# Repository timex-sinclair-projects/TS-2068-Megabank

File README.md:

# TS-2068 Megabank

A battery-backed 4 MB RAM board for the Timex Sinclair 2068, built the way
Timex meant memory to grow: as **expansion banks** that can take over any 8K
chunk of the address space. It is a card for the expansion bus, for owners
of the TS-Pico v3.

It gives the 2068:

- **Paged memory:** any 8K page of the 4 MB, mapped into any chunk with two
  `OUT`s, at full memory speed.
- **A RAM disk:** `SAVE "r:name"`, `LOAD "r:name"`, `CAT "r:"` and the rest,
  kept through power-off by a battery.

**Status:** design. Nothing is built yet. Start with the
[specification](docs/spec.md); the board's KiCad project (schematic done,
routed on the TS-Pico v3's form factor, DRC clean, not yet ordered) is in
[hardware/](hardware/README.md).

*The routed card (KiCad render, 2026-11-07), the same 130 × 64 mm shape as
the TS-Pico v3. Underside: [docs/images/megabank-bottom.png](docs/images/megabank-bottom.png).*

## Where the work lives

| Part | Repository |
|---|---|
| The board: schematic, PCB, the controller's firmware | here |
| The TS-Pico ROM (detection, the RAM disk's copy routine, `r:`, the Timex bank API) and the v3 firmware (bus sharing, the RAM disk's file system) | [tspico-firmware-build](https://github.com/timex-sinclair-projects/tspico-firmware-build) |
| PicoVideo's support (ignoring screen writes to mapped banks) | [PicoVideo](https://github.com/timex-sinclair-projects/PicoVideo) |
| The emulator model | [zesarux-tspico](https://github.com/timex-sinclair-projects/zesarux-tspico) |

## The first test

Does a 2068 answer the board's ports, FCh and FDh? With nothing plugged in:

```
OUT 252,2: OUT 253,2: PRINT IN 252, IN 253
```

The border should not change, and nothing should answer either port.

**Result (2026-10-16), with the TS-Pico fitted:** the border did not change,
and both ports drift between 127 and 255 from one read to the next whatever
keys are held: a floating bus, with nothing answering. FCh and FDh stand.

## Licences

| What | Licence | File |
|---|---|---|
| Hardware design files: schematic and PCB | CERN Open Hardware Licence v2, Permissive (CERN-OHL-P-2.0) | [LICENSE-hardware.txt](LICENSE-hardware.txt) |
| Software: the board's controller firmware (RP2350B), tools and test programs | MIT | [LICENSE](LICENSE) |
| Documentation (`docs/`, this README) | Creative Commons Attribution 4.0 (CC BY 4.0) | [LICENSE-docs.txt](LICENSE-docs.txt) |

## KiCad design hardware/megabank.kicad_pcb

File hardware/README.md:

# Megabank KiCad project

Status 2026-11-07: **routed, DRC clean at every severity** (no errors, no warnings,
nothing unconnected), not yet ordered. The board has the TS-Pico v3's form factor
and is built with v3's script pipeline (tspico-hardware, `hardware/scripts/`),
copied here and renamed. Spec: [../docs/spec.md](../docs/spec.md).

- **Schematic:** four sheets, generated. ERC: one warning, expected (below).
- **Board:** outline, gold fingers and mounting holes are v3's. Routed by
  `scripts/flow.py` with Freerouting 2.4.1 and no hand edits: 1945 track
  segments (1315 top, 630 bottom), 355 vias, all 0.6/0.3 mm, narrowest track
  0.11 mm, nothing on the plane layers. Closed on the first attempt (re-routed
  2026-11-07 for the core LDO, which replaced the RP2350B's switcher and L1,
  and the GPIO46/47 test pads). Silkscreen: all 90 designators placed.
- **Fab files:** `python3 scripts/gen_fab.py` writes the Gerbers, BOM and CPL
  to `fab/jlcpcb/`, committed: `megabank-gerbers.zip`, `megabank-bom.csv`,
  `megabank-cpl.csv`, ready to upload as they are (the unzipped Gerbers are not
  committed); `fab/NOTES.md` lists what to check on upload.
- **Parts:** every fitted part has an LCSC number. $26.63 a board in parts at
  10 boards (`jlc_price.py`, 2026-11-07; it counts U1-U4 once, so about $27),
  plus $45 in extended-part fees once; the two SRAMs are $20.86 of it. The
  ME6211C12 LDO (32,146 in stock) is an extended part like the L1 it replaced.

## Form factor

The same card as v3, so the two share the extender, brackets and standoffs:

| Item | Value |
|---|---|
| Board | 130.00 x 64.25 mm, 1.6 mm, 4 layers (JLC04161H-7628): F.Cu, In1 GND, In2 +3V3, B.Cu |
| Body | 130.00 x 56.00 mm |
| Tongue | 83.66 x 8.25 mm, left edge 18.48 mm from the board's left edge, 1 mm chamfers |
| Fingers | `TS2068_EdgeConnector_2x32`, 32 positions at 2.54 mm, 31 a side, key slot at position 6 |
| Holes | M3 at (5, 5), (113.6, 4.2), (5, 51), (112, 51.5): v3's |

The finger geometry and the side-A-is-top assumption are v3's; see v3's
`hardware/README.md`, "Edge connector geometry". Check side A before ordering
(spec, open question 6).

## Sheets

| Sheet | Generator | Contents |
|---|---|---|
| `megabank.kicad_sch` | by hand | Root: four sheets, flat, global labels |
| `interface.kicad_sch` | `gen_interface.py` | P1 fingers; U1/U2 address buffers (always on: BA0-BA15), U3 data buffer (DIR = /RD, /OE = nDOE), U4 control buffer; U5 74LVC1G06 /BE driver; U6 74LVC1G06 /NMI driver; U7 74LVC2G34 /INT and /NMI in; pulls R1-R4 |
| `memory.kicad_sch` | `gen_memory.py` | U10/U11 CY62167EV30 as 2M x 8; U12 /WE gate; ~CE1 pull-downs, WINH pull-up, BHE/BLE links |
| `mcu.kicad_sch` | `gen_mcu.py` | v3's RP2350B core, same designators, but DVDD from U23, a 1.2 V LDO (no L1); USB-C; RUN, BOOTSEL; SW5 write protect; TP4/TP5 on the spare GPIOs; the GPIO map |
| `power.kicad_sch` | `gen_power.py` | +5V diode-OR (edge, USB), TLV1117LV33, TPS3839 -> CE2, LM66200 -> VSRAM, CR2032, battery monitor |

`gen_symbols.py` writes `lib/megabank.kicad_sym`: the edge connector (v3's),
the CY62167EV30 (from the Infineon datasheet, 002-24706 Rev \*B, figure 2) and
the LM66200 (TI SLVSG04, table 5-1). `parts.py` maps value and footprint to MPN
and LCSC number; `schlib.place()` stamps them on each symbol.

### GPIO map

A PIO state machine sees 32 pins, from GPIO0 or GPIO16. The port program needs
data, A0-A7 and the strobes; the memory program needs the chunk bits, the
strobes, /BE, the ~CE1s and the page bits. Everything both need sits in 16-31:

| GPIO | Net | |
|---|---|---|
| 0-7 | SD0-SD7 | SRAM-side data: `IN`/`OUT` to FCh/FDh |
| 8-15 | BA0-BA7 | port decode |
| 16-18 | BA13-BA15 | chunk (`out pc, 3`) |
| 19-25 | nMREQ_L, nIORQ_L, nRD_L, nWR_L, nRFSH_L, nM1_L, nRESET_L | |
| 26 | nDOE | data buffer enable, pulled up |
| 27 | BE_REQ | to U5, pulled down |
| 28-29 | nCE1_0, nCE1_1 | SRAM enables, pulled down |
| 30-37 | PA13-PA20 | page bits, contiguous with the ~CE1s |
| 38 | WINH | write inhibit, pulled up |
| 39 | nWP | write-protect switch, low = protected |
| 40 | BAT_ADC | ADC0 |
| 41 | BAT_EN | |
| 42 | nBE_L | /BE read back through U4's spare channel |
| 43 | nINT_L | /INT, through U7 |
| 44 | nNMI_L | /NMI, through U7 |
| 45 | NMI_REQ | to U6, pulled down (R4) |
| 46-47 | GP46, GP47 | spare, on test pads TP4, TP5 (silk "GP46", "GP47") for bench experiments |

### Decisions taken here, beyond the spec

- **USB-C, as on v3** (open question 11): firmware by BOOTSEL and the settings
  (`BASE`, `SIZE`) over USB. VBUS is diode-ORed with the edge +5V, so the board
  runs from USB alone on the bench. SWD pads TP1-TP3 too.
- **/BE read back:** U4's eighth channel brings /BE in as nBE_L (GPIO42), for
  timing on the bench and to see v3 serve a chunk.
- **BT1 is a Keystone 3034TR** (C5213768, 2026-11-07), the footprint's own
  part, as on the OpenSpand card, where JLCPCB placed it. The Q&J
  CR2032-BS-6-1 (C70377) made JLCPCB move the order to Standard PCBA (edge
  rails, which would sit against the fingers). Stock is thin (654); if it runs
  out, leave BT1 off and fit a Keystone 3034 from DigiKey (36-3034-ND) by hand.
- **R3, a /BE pull-up to +5V_EDGE, DNP** (open question 13): the bus already has
  v3's 2k2; the pad is there if the prototype shows /BE rising too slowly.
- **An LDO for the core, not the on-chip switcher** (2026-11-07): U23, an
  ME6211C12M5G-N (SOT-23-5, C236672), supplies DVDD at 1.2 V, as on the
  OpenSpand card. The switcher's inductor (v3's L1, Abracon
  AOTA-B201610S3R3-101-T) was the scarcest part on the board (3 at JLCPCB in
  October) and needed a pre-order or hand fitting. VREG_LX is open, VREG_FB is
  grounded, VREG_VIN (C22) and VREG_AVDD (R28/C39) stay powered (RP2350
  datasheet 6.3.7). 1.2 V is what v3's firmware sets for 250 MHz; the firmware
  may put the unused regulator in HIZ to save about 400 µA. C40 (1 µF) at the
  LDO's input, C20 (4.7 µF) at its output; C21/C47/C48 stay at DVDD pins 51,
  32 and 10.
- **Test pads on the spare GPIOs:** TP4 (GPIO46) and TP5 (GPIO47), for bench
  experiments such as a second controller's handshake (spec, Bus mastering).
- **One 0 R each for BHE and BLE** (R13, R14), shared by both chips.
- **Battery-monitor designators** are R51-R54, C55 (the spec's R1-R4, C1).
- **SRAM pins may be swapped at layout:** any permutation of A0-A20 or of
  I/O0-I/O7 is harmless, since both chips always see the same mapping. Only
  SDn must stay on GPIOn. Worth using if the router struggles.

### The ERC warning

`U5 pin 4 (open collector) and U4 pin 18 (tri-state)`: the /BE driver and the
buffer that reads /BE back. That is the intent.

## Layout

Coordinates in mm from the body's top-left corner (`gen_layout.py`, table `P`).

- **Over the fingers,** as v3: data U3 (x 40), high address U2 (x 63) over
  A15-A8, control U4 (x 80) over /MREQ to /RFSH, /BE driver U5 by finger A29.
  /INT and /NMI over their fingers (A14, A15) between C3 and U2: U7 (x 51.5),
  U6 and R4 (x 56.5).
  Low address U1 above U2.
- **RP2350B cluster** at v3's coordinates with v3's designators (U20 at
  (62, 26), 90°), so v3's crystal and fan-out pre-routes carry over. Flash U21
  to its left.
- **Core supply:** with VREG_FB grounded, pin 51 is the only DVDD pin a track
  can reach from outside the pad ring (on v3 the switcher's output came in
  through FB). So the LDO U23 sits above pin 51, at (60.55, 14.6), pins 4/5
  towards the chip: its output runs straight down to pin 51, 0.3 mm wide,
  past C21, with C20 off its side, and v3's DVDD spine under the package
  carries it on to pins 10 and 32. C40 above U23; plane vias for its input
  and ground. FB goes to a GND via where L1 was. TP4/TP5 at (53.5, 13.5) and
  (53.5, 16), up and left of the chip's GPIO46/47 pins.
  One pre-route changed: on v3, supply pin 29 dropped into the lanes of pads 27
  and 28 to reach its via, because those GPIOs (26, 27) were spare. Here they
  are nDOE and BE_REQ, and the first run left both sealed in on all three
  attempts. The 24/29 supply link now carries on under the package to pin 15,
  whose fan via is already on the +3V3 plane.
- **SRAM** U10 and U11 on the right, leads top and bottom; the /WE gate, the
  supervisor and the pulls in the strip between them and the crystal.
- **Power:** diodes and LDO top left, LM66200 and the battery monitor in the
  free strip above the RP2350B, the CR2032 bottom left. USB-C on the left edge
  (v3's place). RUN and BOOTSEL on the top edge (v3's places). Write-protect
  slide switch on the right edge.

## Next

1. **Check footprints against drawings:** the MSK12C02's
   actuator should face the right edge; TSOP-I 48 against Infineon's 51-85183.
   Then check side A of the fingers (spec, open question 6).
2. **The SRAM rail with a fresh cell:** the LM66200 passes whichever input is
   higher, and a new CR2032 reads up to about 3.3 V open circuit, against +3V3's
   3.25-3.35 V. At SRAM standby currents the cell may carry the rail some of the
   time with the 2068 on. Harmless to the data; it costs battery life. Measure on
   the prototype (spec, hardware test 3); a Schottky in series with the cell
   would settle it if needed.
3. **Stock:** 42 CY62167EV30 at JLCPCB on 2026-10-18, 40 on 2026-11-07, enough for 20 boards.

## Routing

```bash
cd hardware
PY=/Applications/KiCad/KiCad.app/Contents/Frameworks/Python.framework/Versions/Current/bin/python3
$PY scripts/flow.py                                   # jar from $FREEROUTING_JAR (or --jar); needs Homebrew's openjdk
scripts/check.sh                                      # ERC (one expected warning) and DRC
python3 scripts/gen_fab.py
```

`flow.py` regenerates the placement and discards all routing, then pre-routes,
autoroutes, finishes and places silkscreen, up to three attempts; Freerouting
does not give the same result twice. Each attempt took 4-8 minutes to route
here. A failed attempt is kept as `fab/route/attempt-N.kicad_pcb`.

## Regenerating

```bash
cd hardware
python3 scripts/gen_symbols.py                       # project symbols
for s in interface memory mcu power; do python3 scripts/gen_$s.py; done
PY=/Applications/KiCad/KiCad.app/Contents/Frameworks/Python.framework/Versions/Current/bin/python3
$PY scripts/gen_layout.py                            # skeleton, netlist, placement, planes (discards routing)
$PY scripts/preroute.py                              # v3's locked pre-routes
```

Regenerating a sheet overwrites hand edits; once a sheet is edited in KiCad,
retire its generator. The same goes for `gen_layout.py` once routing starts by
hand.

BOM and price:

```bash
cd hardware
KC=/Applications/KiCad/KiCad.app/Contents/MacOS/kicad-cli
$KC sch export bom --output bom/megabank-jlcpcb-bom.csv --fields "Value,Reference,Footprint,LCSC" --labels "Comment,Designator,Footprint,LCSC Part #" --group-by "Value,Footprint" --exclude-dnp megabank.kicad_sch
python3 scripts/jlc_price.py --boards 10 --bom bom/megabank-jlcpcb-bom.csv
```

(`jlc_price.py` counts a range like `U1-U4` as one part, so its total runs a
little low.)

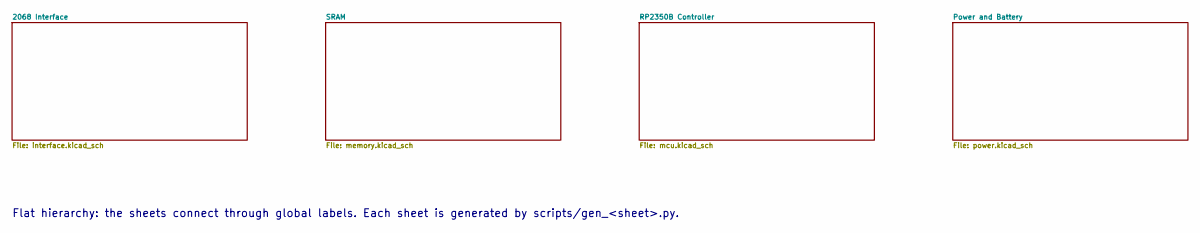
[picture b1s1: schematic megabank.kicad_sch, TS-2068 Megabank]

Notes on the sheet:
Flat hierarchy: the sheets connect through global labels. Each sheet is generated by scripts/gen_<sheet>.py.

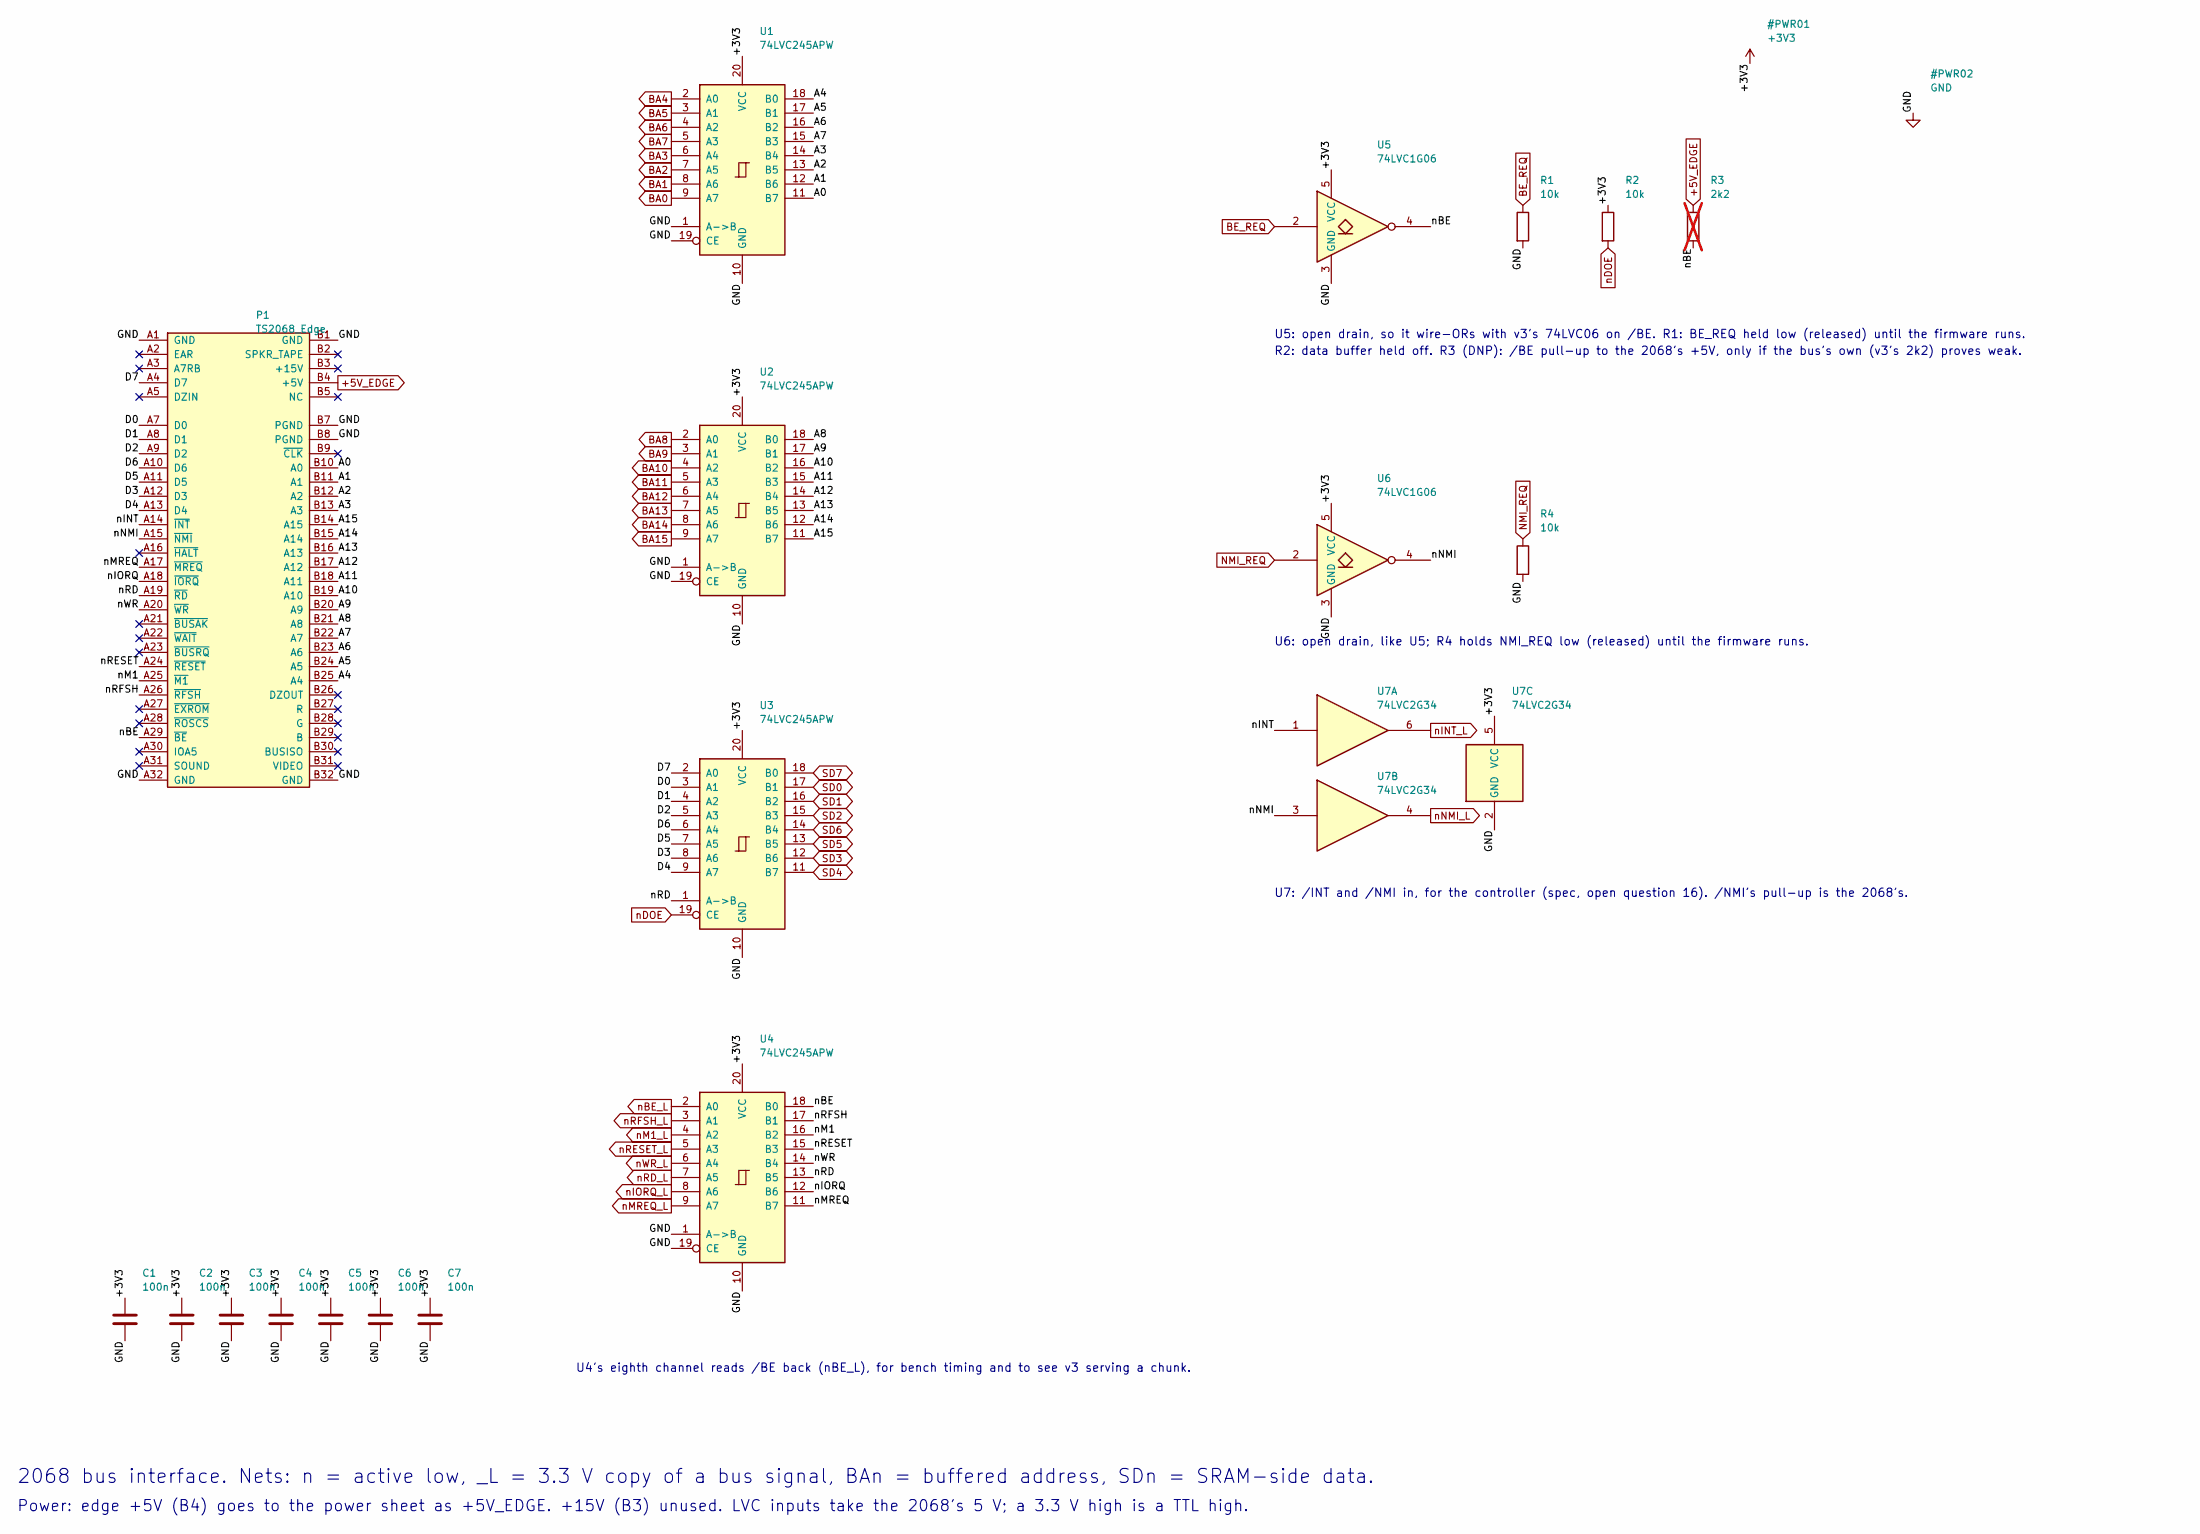
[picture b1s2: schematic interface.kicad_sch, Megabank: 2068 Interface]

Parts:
C1, C2, C3, C4, C5, C6, C7: 100n; C_0603_1608Metric; MPN CC0603KRX7R9BB104; LCSC C14663
P1: TS2068_Edge; TS2068_EdgeConnector_2x32
R1, R2, R4: 10k; R_0603_1608Metric; MPN 0603WAF1002T5E; LCSC C25804
R3: 2k2; R_0603_1608Metric; MPN 0603WAF2201T5E; LCSC C4190; not fitted
U1, U2, U3, U4: 74LVC245APW; TSSOP-20_4.4x6.5mm_P0.65mm; MPN 74LVC245APW,118; LCSC C6082
U5, U6: 74LVC1G06; SOT-353_SC-70-5; MPN SN74LVC1G06DCKR; LCSC C7828
U7: 74LVC2G34; SOT-363_SC-70-6; MPN SN74LVC2G34DCKR; LCSC C14461

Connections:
+3V3: C1.1, C2.1, C3.1, C4.1, C5.1, C6.1, C7.1, R2.1, U1.20 (VCC), U2.20 (VCC), U3.20 (VCC), U4.20 (VCC), U5.5 (VCC), U6.5 (VCC), U7.5 (VCC); also elsewhere on the board
+5V_EDGE: P1.B4 (+5V), R3.1; also elsewhere on the board
/2068 Interface/A0: P1.B10 (A0), U1.11 (B7)
/2068 Interface/A1: P1.B11 (A1), U1.12 (B6)
/2068 Interface/A2: P1.B12 (A2), U1.13 (B5)
/2068 Interface/A3: P1.B13 (A3), U1.14 (B4)
/2068 Interface/A4: P1.B25 (A4), U1.18 (B0)
/2068 Interface/A5: P1.B24 (A5), U1.17 (B1)
/2068 Interface/A6: P1.B23 (A6), U1.16 (B2)
/2068 Interface/A7: P1.B22 (A7), U1.15 (B3)
/2068 Interface/A8: P1.B21 (A8), U2.18 (B0)
/2068 Interface/A9: P1.B20 (A9), U2.17 (B1)
/2068 Interface/A10: P1.B19 (A10), U2.16 (B2)
/2068 Interface/A11: P1.B18 (A11), U2.15 (B3)
/2068 Interface/A12: P1.B17 (A12), U2.14 (B4)
/2068 Interface/A13: P1.B16 (A13), U2.13 (B5)
/2068 Interface/A14: P1.B15 (A14), U2.12 (B6)
/2068 Interface/A15: P1.B14 (A15), U2.11 (B7)
/2068 Interface/D0: P1.A7 (D0), U3.3 (A1)
/2068 Interface/D1: P1.A8 (D1), U3.4 (A2)
/2068 Interface/D2: P1.A9 (D2), U3.5 (A3)
/2068 Interface/D3: P1.A12 (D3), U3.8 (A6)
/2068 Interface/D4: P1.A13 (D4), U3.9 (A7)
/2068 Interface/D5: P1.A11 (D5), U3.7 (A5)
/2068 Interface/D6: P1.A10 (D6), U3.6 (A4)
/2068 Interface/D7: P1.A4 (D7), U3.2 (A0)
/2068 Interface/nBE: P1.A29 (~BE), R3.2, U4.18 (B0), U5.4
/2068 Interface/nINT: P1.A14 (~INT), U7.1
/2068 Interface/nIORQ: P1.A18 (~IORQ), U4.12 (B6)
/2068 Interface/nM1: P1.A25 (~M1), U4.16 (B2)
/2068 Interface/nMREQ: P1.A17 (~MREQ), U4.11 (B7)
/2068 Interface/nNMI: P1.A15 (~NMI), U6.4, U7.3
/2068 Interface/nRD: P1.A19 (~RD), U3.1 (A->B), U4.13 (B5)
/2068 Interface/nRESET: P1.A24 (~RESET), U4.15 (B3)
/2068 Interface/nRFSH: P1.A26 (~RFSH), U4.17 (B1)
/2068 Interface/nWR: P1.A20 (~WR), U4.14 (B4)
BA0: U1.9 (A7); also elsewhere on the board
BA1: U1.8 (A6); also elsewhere on the board
BA2: U1.7 (A5); also elsewhere on the board
BA3: U1.6 (A4); also elsewhere on the board
BA4: U1.2 (A0); also elsewhere on the board
BA5: U1.3 (A1); also elsewhere on the board
BA6: U1.4 (A2); also elsewhere on the board
BA7: U1.5 (A3); also elsewhere on the board
BA8: U2.2 (A0); also elsewhere on the board
BA9: U2.3 (A1); also elsewhere on the board
BA10: U2.4 (A2); also elsewhere on the board
BA11: U2.5 (A3); also elsewhere on the board
BA12: U2.6 (A4); also elsewhere on the board
BA13: U2.7 (A5); also elsewhere on the board
BA14: U2.8 (A6); also elsewhere on the board
BA15: U2.9 (A7); also elsewhere on the board
BE_REQ: R1.1, U5.2; also elsewhere on the board
GND: C1.2, C2.2, C3.2, C4.2, C5.2, C6.2, C7.2, P1.A1 (GND), P1.A32 (GND), P1.B1 (GND), P1.B7 (PGND), P1.B8 (PGND), P1.B32 (GND), R1.2, R4.2, U1.1 (A->B), U1.10 (GND), U1.19 (CE), U2.1 (A->B), U2.10 (GND), U2.19 (CE), U3.10 (GND), U4.1 (A->B), U4.10 (GND), U4.19 (CE), U5.3 (GND), U6.3 (GND), U7.2 (GND); also elsewhere on the board
NMI_REQ: R4.1, U6.2; also elsewhere on the board
SD0: U3.17 (B1); also elsewhere on the board
SD1: U3.16 (B2); also elsewhere on the board
SD2: U3.15 (B3); also elsewhere on the board
SD3: U3.12 (B6); also elsewhere on the board
SD4: U3.11 (B7); also elsewhere on the board
SD5: U3.13 (B5); also elsewhere on the board
SD6: U3.14 (B4); also elsewhere on the board
SD7: U3.18 (B0); also elsewhere on the board
nBE_L: U4.2 (A0); also elsewhere on the board
nDOE: R2.2, U3.19 (CE); also elsewhere on the board
nINT_L: U7.6; also elsewhere on the board
nIORQ_L: U4.8 (A6); also elsewhere on the board
nM1_L: U4.4 (A2); also elsewhere on the board
nMREQ_L: U4.9 (A7); also elsewhere on the board
nNMI_L: U7.4; also elsewhere on the board
nRD_L: U4.7 (A5); also elsewhere on the board
nRESET_L: U4.5 (A3); also elsewhere on the board
nRFSH_L: U4.3 (A1); also elsewhere on the board
nWR_L: U4.6 (A4); also elsewhere on the board

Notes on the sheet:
2068 bus interface. Nets: n = active low, _L = 3.3 V copy of a bus signal, BAn = buffered address, SDn = SRAM-side data.
Power: edge +5V (B4) goes to the power sheet as +5V_EDGE. +15V (B3) unused. LVC inputs take the 2068's 5 V; a 3.3 V high is a TTL high.
U4's eighth channel reads /BE back (nBE_L), for bench timing and to see v3 serving a chunk.
U5: open drain, so it wire-ORs with v3's 74LVC06 on /BE. R1: BE_REQ held low (released) until the firmware runs.
R2: data buffer held off. R3 (DNP): /BE pull-up to the 2068's +5V, only if the bus's own (v3's 2k2) proves weak.
U6: open drain, like U5; R4 holds NMI_REQ low (released) until the firmware runs.
U7: /INT and /NMI in, for the controller (spec, open question 16). /NMI's pull-up is the 2068's.

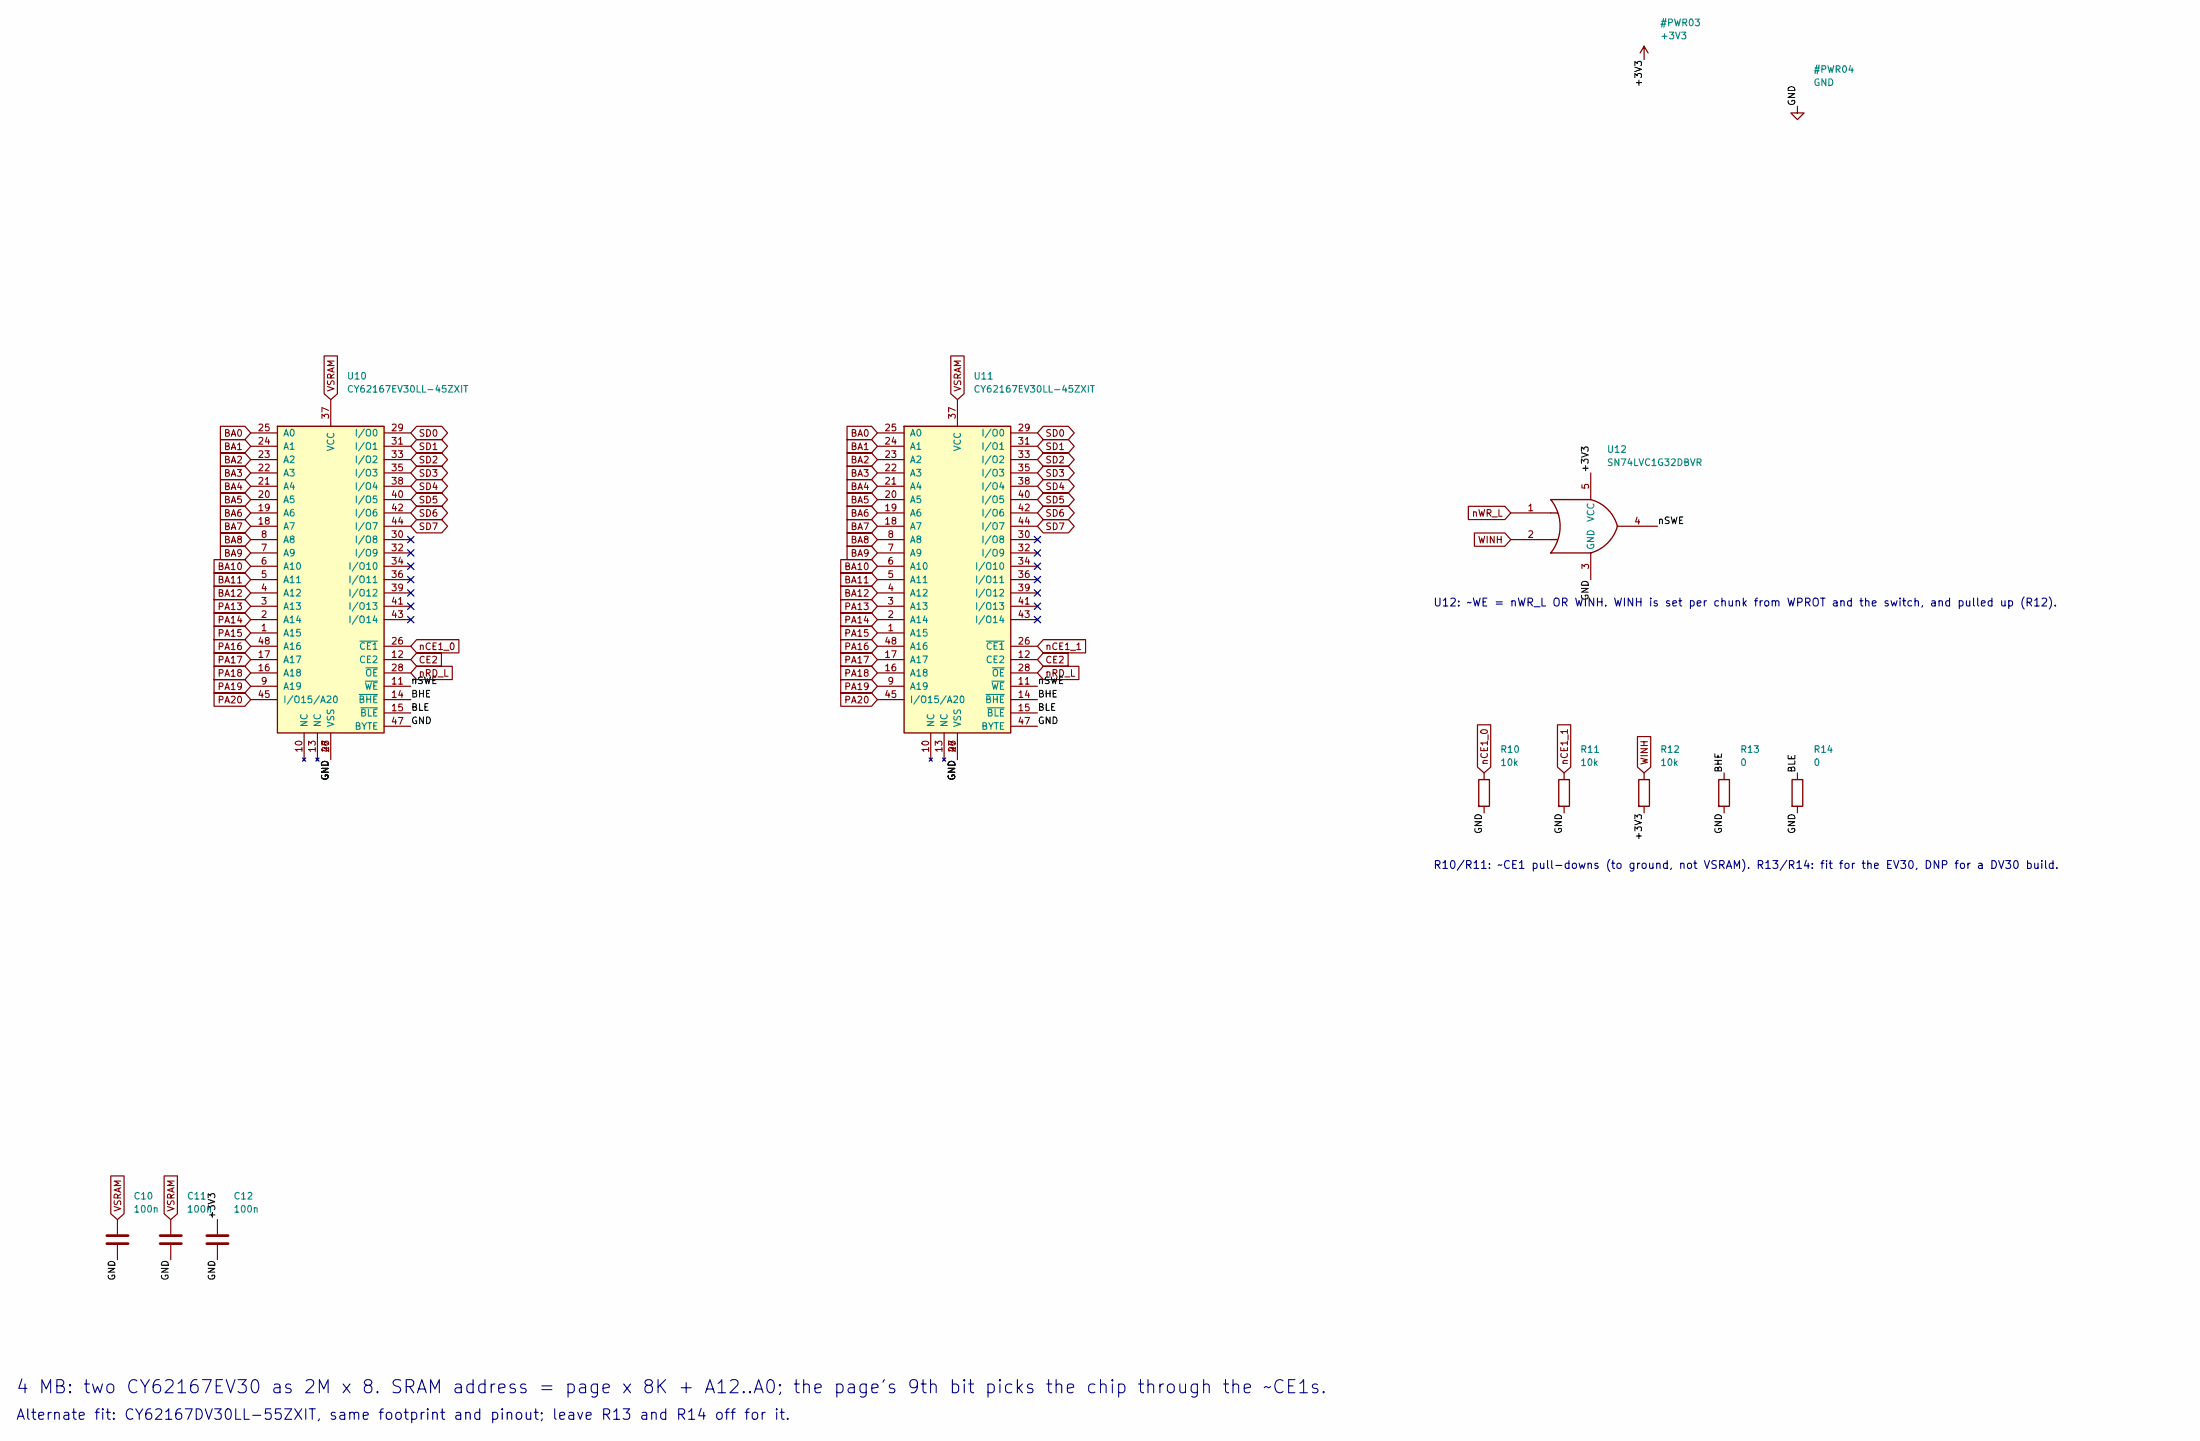
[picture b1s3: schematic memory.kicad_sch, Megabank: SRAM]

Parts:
C10, C11, C12: 100n; C_0603_1608Metric; MPN CC0603KRX7R9BB104; LCSC C14663
R10, R11, R12: 10k; R_0603_1608Metric; MPN 0603WAF1002T5E; LCSC C25804
R13, R14: 0; R_0603_1608Metric; MPN 0603WAF0000T5E; LCSC C21189
U10, U11: CY62167EV30LL-45ZXIT; TSOP-I-48_18.4x12mm_P0.5mm; MPN CY62167EV30LL-45ZXIT; LCSC C511152
U12: SN74LVC1G32DBVR; SOT-23-5; MPN SN74LVC1G32DBVR; LCSC C10096

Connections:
+3V3: C12.1, R12.2, U12.5 (VCC); also elsewhere on the board
/SRAM/BHE: R13.1, U10.14 (~BHE), U11.14 (~BHE)
/SRAM/BLE: R14.1, U10.15 (~BLE), U11.15 (~BLE)
/SRAM/nSWE: U10.11 (~WE), U11.11 (~WE), U12.4
BA0: U10.25 (A0), U11.25 (A0); also elsewhere on the board
BA1: U10.24 (A1), U11.24 (A1); also elsewhere on the board
BA2: U10.23 (A2), U11.23 (A2); also elsewhere on the board
BA3: U10.22 (A3), U11.22 (A3); also elsewhere on the board
BA4: U10.21 (A4), U11.21 (A4); also elsewhere on the board
BA5: U10.20 (A5), U11.20 (A5); also elsewhere on the board
BA6: U10.19 (A6), U11.19 (A6); also elsewhere on the board
BA7: U10.18 (A7), U11.18 (A7); also elsewhere on the board
BA8: U10.8 (A8), U11.8 (A8); also elsewhere on the board
BA9: U10.7 (A9), U11.7 (A9); also elsewhere on the board
BA10: U10.6 (A10), U11.6 (A10); also elsewhere on the board
BA11: U10.5 (A11), U11.5 (A11); also elsewhere on the board
BA12: U10.4 (A12), U11.4 (A12); also elsewhere on the board
CE2: U10.12 (CE2), U11.12 (CE2); also elsewhere on the board
GND: C10.2, C11.2, C12.2, R10.2, R11.2, R13.2, R14.2, U10.27 (VSS), U10.46 (VSS), U10.47 (BYTE), U11.27 (VSS), U11.46 (VSS), U11.47 (BYTE), U12.3 (GND); also elsewhere on the board
PA13: U10.3 (A13), U11.3 (A13); also elsewhere on the board
PA14: U10.2 (A14), U11.2 (A14); also elsewhere on the board
PA15: U10.1 (A15), U11.1 (A15); also elsewhere on the board
PA16: U10.48 (A16), U11.48 (A16); also elsewhere on the board
PA17: U10.17 (A17), U11.17 (A17); also elsewhere on the board
PA18: U10.16 (A18), U11.16 (A18); also elsewhere on the board
PA19: U10.9 (A19), U11.9 (A19); also elsewhere on the board
PA20: U10.45 (I/O15/A20), U11.45 (I/O15/A20); also elsewhere on the board
SD0: U10.29 (I/O0), U11.29 (I/O0); also elsewhere on the board
SD1: U10.31 (I/O1), U11.31 (I/O1); also elsewhere on the board
SD2: U10.33 (I/O2), U11.33 (I/O2); also elsewhere on the board
SD3: U10.35 (I/O3), U11.35 (I/O3); also elsewhere on the board
SD4: U10.38 (I/O4), U11.38 (I/O4); also elsewhere on the board
SD5: U10.40 (I/O5), U11.40 (I/O5); also elsewhere on the board
SD6: U10.42 (I/O6), U11.42 (I/O6); also elsewhere on the board
SD7: U10.44 (I/O7), U11.44 (I/O7); also elsewhere on the board
VSRAM: C10.1, C11.1, U10.37 (VCC), U11.37 (VCC); also elsewhere on the board
WINH: R12.1, U12.2; also elsewhere on the board
nCE1_0: R10.1, U10.26 (~CE1); also elsewhere on the board
nCE1_1: R11.1, U11.26 (~CE1); also elsewhere on the board
nRD_L: U10.28 (~OE), U11.28 (~OE); also elsewhere on the board
nWR_L: U12.1; also elsewhere on the board

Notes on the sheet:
4 MB: two CY62167EV30 as 2M x 8. SRAM address = page x 8K + A12..A0; the page's 9th bit picks the chip through the ~CE1s.
Alternate fit: CY62167DV30LL-55ZXIT, same footprint and pinout; leave R13 and R14 off for it.
U12: ~WE = nWR_L OR WINH. WINH is set per chunk from WPROT and the switch, and pulled up (R12).
R10/R11: ~CE1 pull-downs (to ground, not VSRAM). R13/R14: fit for the EV30, DNP for a DV30 build.

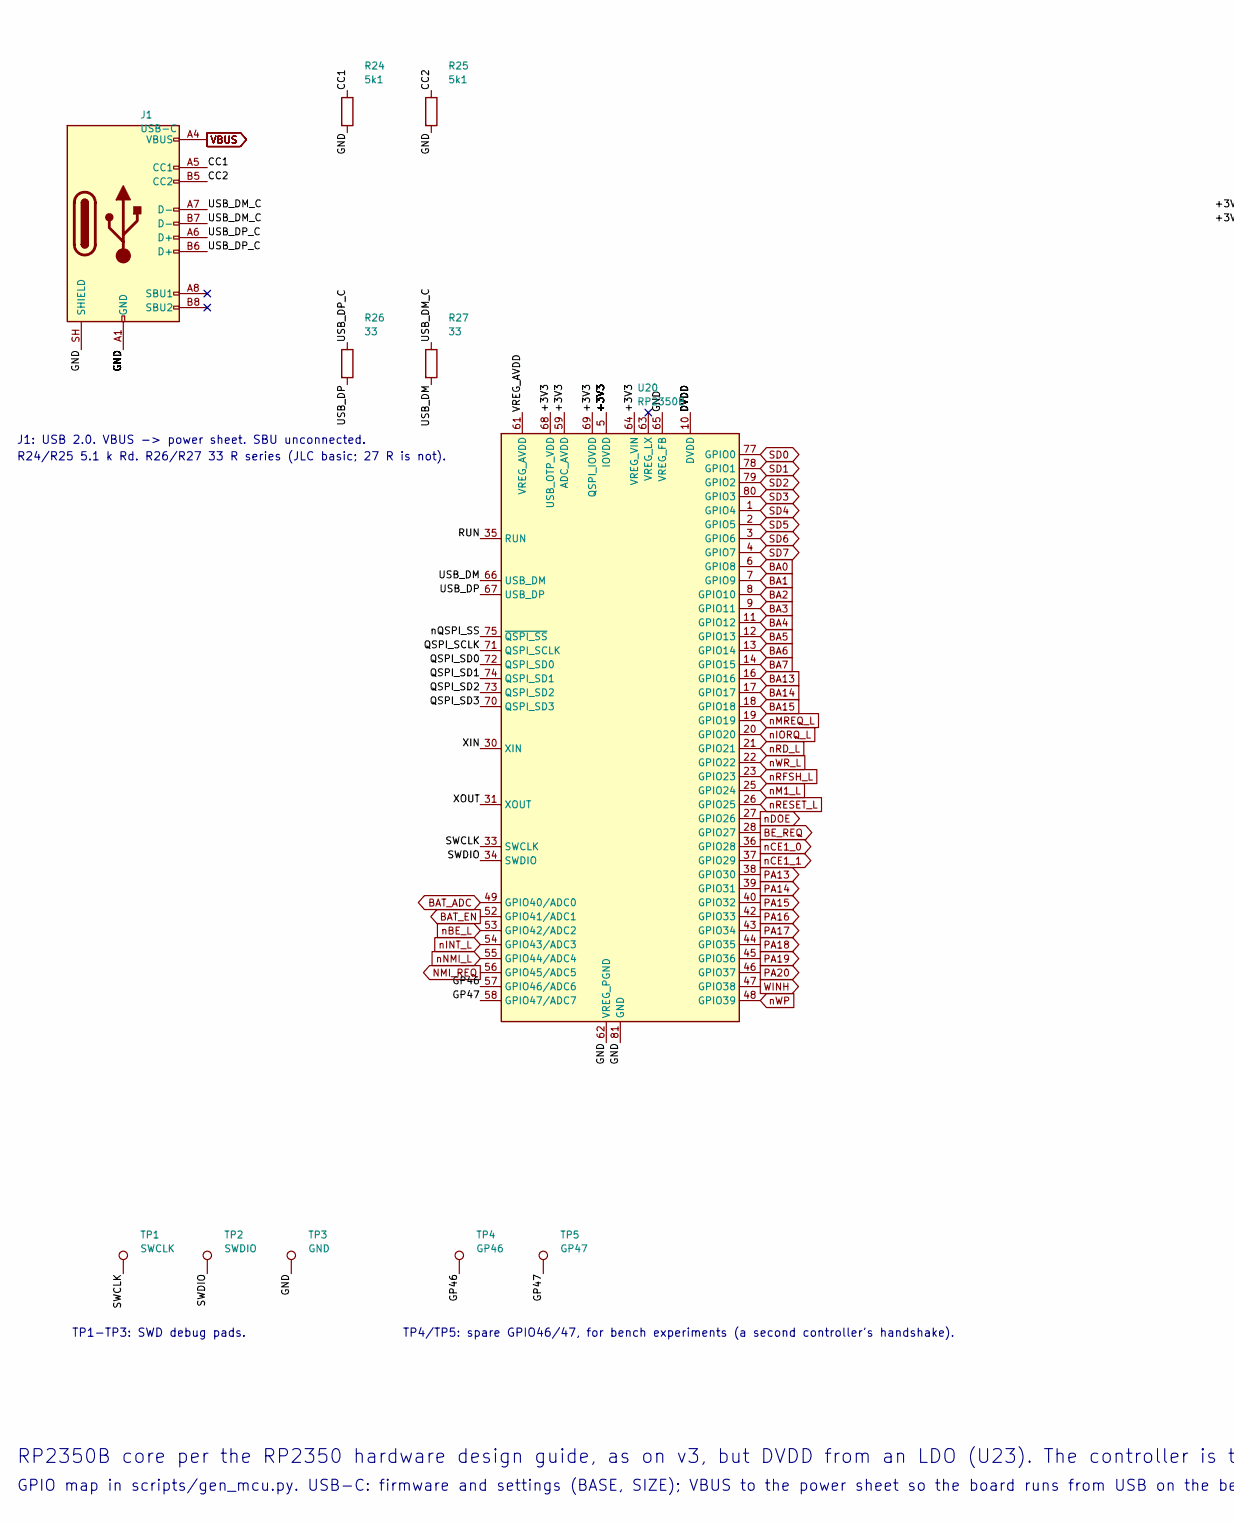
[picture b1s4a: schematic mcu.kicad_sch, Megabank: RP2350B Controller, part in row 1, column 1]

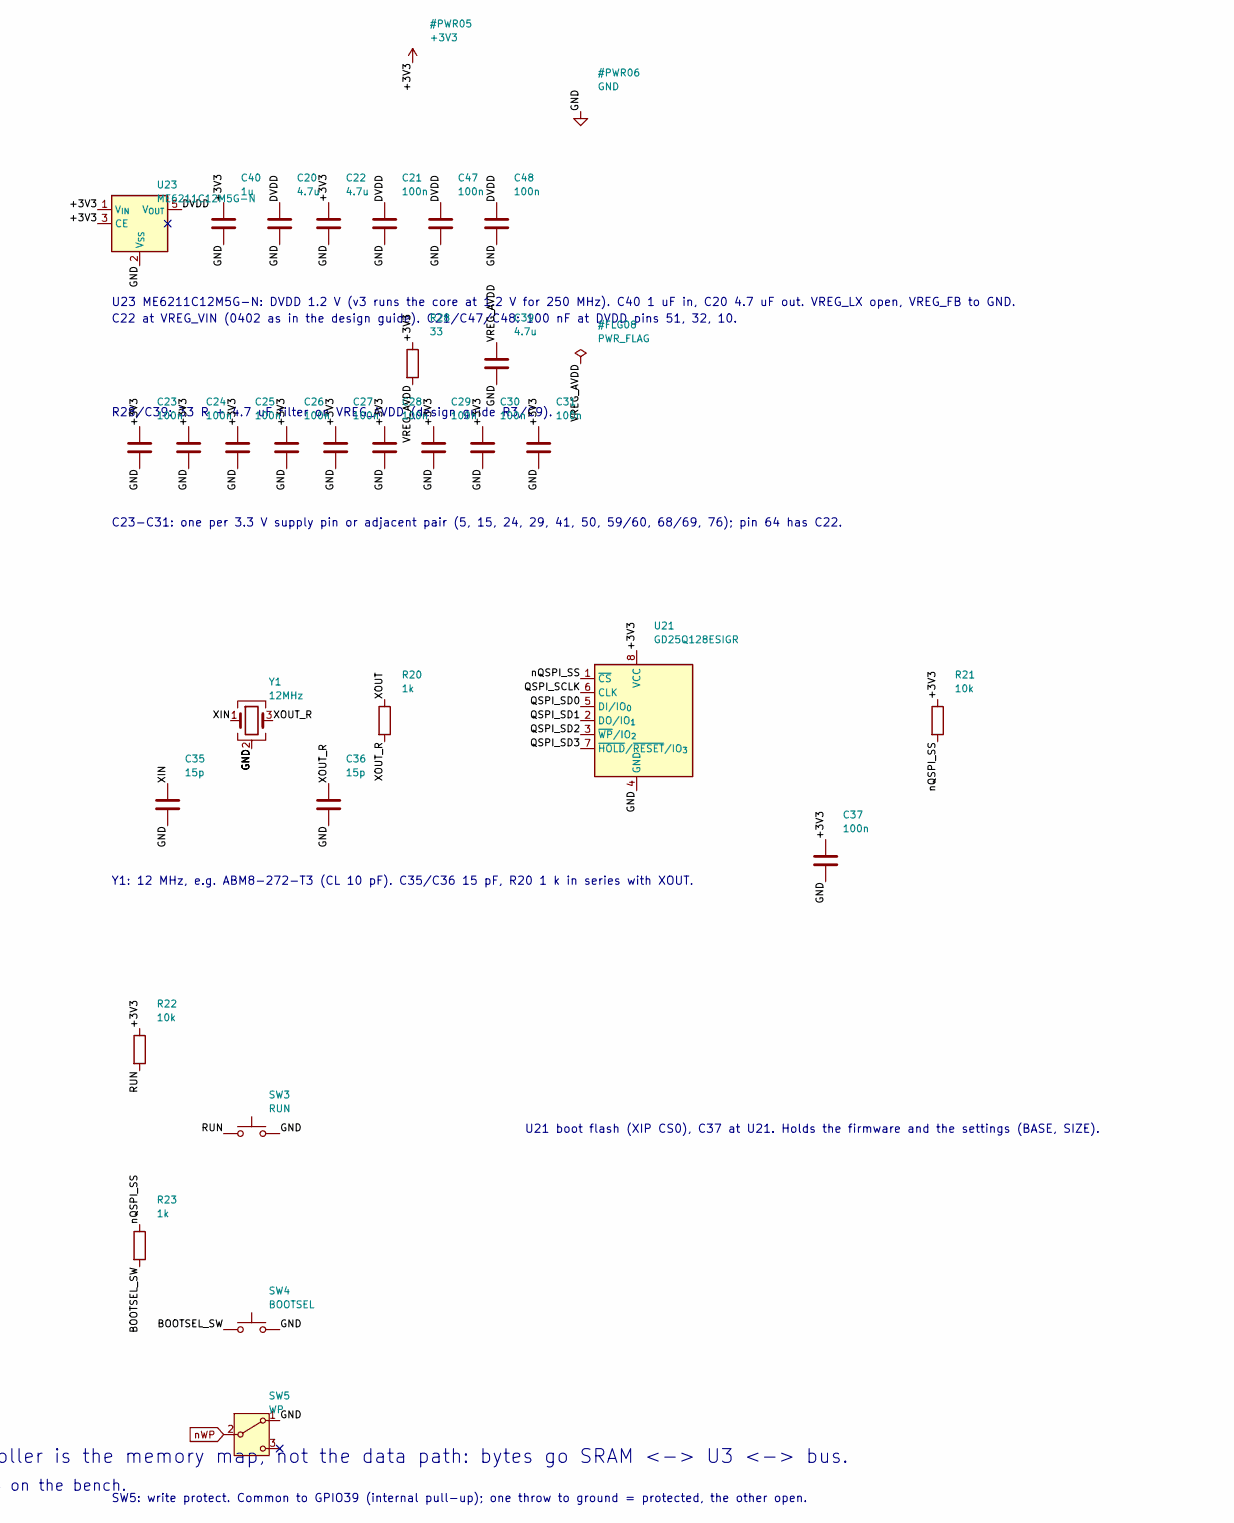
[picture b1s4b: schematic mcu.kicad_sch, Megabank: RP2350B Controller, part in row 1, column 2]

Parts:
C20, C22, C39: 4.7u; C_0402_1005Metric; MPN CL05A475MP5NRNC; LCSC C23733
C21, C23, C24, C25, C26, C27, C28, C29, C30, C31, C37, C47, C48: 100n; C_0603_1608Metric; MPN CC0603KRX7R9BB104; LCSC C14663
C35, C36: 15p; C_0603_1608Metric; MPN CL10C150JB8NNNC; LCSC C1644
C40: 1u; C_0603_1608Metric; MPN CL10A105KB8NNNC; LCSC C15849
J1: USB-C; USB_C_Receptacle_HRO_TYPE-C-31-M-12; MPN TYPE-C-31-M-12; LCSC C165948
R20, R23: 1k; R_0603_1608Metric; MPN 0603WAF1001T5E; LCSC C21190
R21, R22: 10k; R_0603_1608Metric; MPN 0603WAF1002T5E; LCSC C25804
R24, R25: 5k1; R_0603_1608Metric; MPN 0603WAF5101T5E; LCSC C23186
R26, R27, R28: 33; R_0603_1608Metric; MPN 0603WAF330JT5E; LCSC C23140
SW3: RUN; SW_Push_1P1T_XKB_TS-1187A; MPN TS-1187A-B-A-B; LCSC C318884
SW4: BOOTSEL; SW_Push_1P1T_XKB_TS-1187A; MPN TS-1187A-B-A-B; LCSC C318884
SW5: WP; SW_SPDT_Shouhan_MSK12C02; MPN MSK12C02; LCSC C431540
TP1: SWCLK; TestPoint_Pad_1.5x1.5mm
TP2: SWDIO; TestPoint_Pad_1.5x1.5mm
TP3: GND; TestPoint_Pad_1.5x1.5mm
TP4: GP46; TestPoint_Pad_1.5x1.5mm
TP5: GP47; TestPoint_Pad_1.5x1.5mm
U20: RP2350B; QFN-80-1EP_10x10mm_P0.4mm_EP3.4x3.4mm; MPN RP2350B; LCSC C42415655
U21: GD25Q128ESIGR; SOIC-8_5.3x5.3mm_P1.27mm; MPN GD25Q128ESIGR; LCSC C2928891
U23: ME6211C12M5G-N; SOT-23-5; MPN ME6211C12M5G-N; LCSC C236672
Y1: 12MHz; Crystal_SMD_3225-4Pin_3.2x2.5mm; MPN ABM8-272-T3; LCSC C20625731

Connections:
+3V3: C22.1, C23.1, C24.1, C25.1, C26.1, C27.1, C28.1, C29.1, C30.1, C31.1, C37.1, C40.1, R21.1, R22.1, R28.1, U20.5 (IOVDD), U20.15 (IOVDD), U20.24 (IOVDD), U20.29 (IOVDD), U20.41 (IOVDD), U20.50 (IOVDD), U20.59 (ADC_AVDD), U20.60 (IOVDD), U20.64 (VREG_VIN), U20.68 (USB_OTP_VDD), U20.69 (QSPI_IOVDD), U20.76 (IOVDD), U21.8 (VCC), U23.1 (V_{IN}), U23.3 (CE); also elsewhere on the board
/RP2350B Controller/BOOTSEL_SW: R23.2, SW4.1
/RP2350B Controller/CC1: J1.A5 (CC1), R24.1
/RP2350B Controller/CC2: J1.B5 (CC2), R25.1
/RP2350B Controller/DVDD: C20.1, C21.1, C47.1, C48.1, U20.10 (DVDD), U20.32 (DVDD), U20.51 (DVDD), U23.5 (V_{OUT})
/RP2350B Controller/GP46: TP4.1, U20.57 (GPIO46/ADC6)
/RP2350B Controller/GP47: TP5.1, U20.58 (GPIO47/ADC7)
/RP2350B Controller/QSPI_SCLK: U20.71 (QSPI_SCLK), U21.6 (CLK)
/RP2350B Controller/QSPI_SD0: U20.72 (QSPI_SD0), U21.5 (DI/IO_{0})
/RP2350B Controller/QSPI_SD1: U20.74 (QSPI_SD1), U21.2 (DO/IO_{1})
/RP2350B Controller/QSPI_SD2: U20.73 (QSPI_SD2), U21.3 (~WP/IO_{2})
/RP2350B Controller/QSPI_SD3: U20.70 (QSPI_SD3), U21.7 (~HOLD/~RESET/IO_{3})
/RP2350B Controller/RUN: R22.2, SW3.1, U20.35 (RUN)
/RP2350B Controller/SWCLK: TP1.1, U20.33 (SWCLK)
/RP2350B Controller/SWDIO: TP2.1, U20.34 (SWDIO)
/RP2350B Controller/USB_DM: R27.2, U20.66 (USB_DM)
/RP2350B Controller/USB_DM_C: J1.A7 (D-), J1.B7 (D-), R27.1
/RP2350B Controller/USB_DP: R26.2, U20.67 (USB_DP)
/RP2350B Controller/USB_DP_C: J1.A6 (D+), J1.B6 (D+), R26.1
/RP2350B Controller/VREG_AVDD: C39.1, R28.2, U20.61 (VREG_AVDD)
/RP2350B Controller/XIN: C35.1, U20.30 (XIN), Y1.1
/RP2350B Controller/XOUT: R20.1, U20.31 (XOUT)
/RP2350B Controller/XOUT_R: C36.1, R20.2, Y1.3
/RP2350B Controller/nQSPI_SS: R21.2, R23.1, U20.75 (~QSPI_SS), U21.1 (~CS)
BA0: U20.6 (GPIO8); also elsewhere on the board
BA1: U20.7 (GPIO9); also elsewhere on the board
BA2: U20.8 (GPIO10); also elsewhere on the board
BA3: U20.9 (GPIO11); also elsewhere on the board
BA4: U20.11 (GPIO12); also elsewhere on the board
BA5: U20.12 (GPIO13); also elsewhere on the board
BA6: U20.13 (GPIO14); also elsewhere on the board
BA7: U20.14 (GPIO15); also elsewhere on the board
BA13: U20.16 (GPIO16); also elsewhere on the board
BA14: U20.17 (GPIO17); also elsewhere on the board
BA15: U20.18 (GPIO18); also elsewhere on the board
BAT_ADC: U20.49 (GPIO40/ADC0); also elsewhere on the board
BAT_EN: U20.52 (GPIO41/ADC1); also elsewhere on the board
BE_REQ: U20.28 (GPIO27); also elsewhere on the board
GND: C20.2, C21.2, C22.2, C23.2, C24.2, C25.2, C26.2, C27.2, C28.2, C29.2, C30.2, C31.2, C35.2, C36.2, C37.2, C39.2, C40.2, C47.2, C48.2, J1.A1 (GND), J1.A12 (GND), J1.B1 (GND), J1.B12 (GND), J1.SH (SHIELD), R24.2, R25.2, SW3.2, SW4.2, SW5.1 (A), TP3.1, U20.62 (VREG_PGND), U20.65 (VREG_FB), U20.81 (GND), U21.4 (GND), U23.2 (V_{SS}), Y1.2 (G), Y1.4 (G); also elsewhere on the board
NMI_REQ: U20.56 (GPIO45/ADC5); also elsewhere on the board
PA13: U20.38 (GPIO30); also elsewhere on the board
PA14: U20.39 (GPIO31); also elsewhere on the board
PA15: U20.40 (GPIO32); also elsewhere on the board
PA16: U20.42 (GPIO33); also elsewhere on the board
PA17: U20.43 (GPIO34); also elsewhere on the board
PA18: U20.44 (GPIO35); also elsewhere on the board
PA19: U20.45 (GPIO36); also elsewhere on the board
PA20: U20.46 (GPIO37); also elsewhere on the board
SD0: U20.77 (GPIO0); also elsewhere on the board
SD1: U20.78 (GPIO1); also elsewhere on the board
SD2: U20.79 (GPIO2); also elsewhere on the board
SD3: U20.80 (GPIO3); also elsewhere on the board
SD4: U20.1 (GPIO4); also elsewhere on the board
SD5: U20.2 (GPIO5); also elsewhere on the board
SD6: U20.3 (GPIO6); also elsewhere on the board
SD7: U20.4 (GPIO7); also elsewhere on the board
VBUS: J1.A4 (VBUS), J1.A9 (VBUS), J1.B4 (VBUS), J1.B9 (VBUS); also elsewhere on the board
WINH: U20.47 (GPIO38); also elsewhere on the board
nBE_L: U20.53 (GPIO42/ADC2); also elsewhere on the board
nCE1_0: U20.36 (GPIO28); also elsewhere on the board
nCE1_1: U20.37 (GPIO29); also elsewhere on the board
nDOE: U20.27 (GPIO26); also elsewhere on the board
nINT_L: U20.54 (GPIO43/ADC3); also elsewhere on the board
nIORQ_L: U20.20 (GPIO20); also elsewhere on the board
nM1_L: U20.25 (GPIO24); also elsewhere on the board
nMREQ_L: U20.19 (GPIO19); also elsewhere on the board
nNMI_L: U20.55 (GPIO44/ADC4); also elsewhere on the board
nRD_L: U20.21 (GPIO21); also elsewhere on the board
nRESET_L: U20.26 (GPIO25); also elsewhere on the board
nRFSH_L: U20.23 (GPIO23); also elsewhere on the board
nWP: SW5.2 (B), U20.48 (GPIO39)
nWR_L: U20.22 (GPIO22); also elsewhere on the board

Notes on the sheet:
RP2350B core per the RP2350 hardware design guide, as on v3, but DVDD from an LDO (U23). The controller is the memory map, not the data path: bytes go SRAM <-> U3 <-> bus.
GPIO map in scripts/gen_mcu.py. USB-C: firmware and settings (BASE, SIZE); VBUS to the power sheet so the board runs from USB on the bench.
U23 ME6211C12M5G-N: DVDD 1.2 V (v3 runs the core at 1.2 V for 250 MHz). C40 1 uF in, C20 4.7 uF out. VREG_LX open, VREG_FB to GND.
C22 at VREG_VIN (0402 as in the design guide). C21/C47/C48: 100 nF at DVDD pins 51, 32, 10.
R28/C39: 33 R + 4.7 uF filter on VREG_AVDD (design guide R3/C9).
C23-C31: one per 3.3 V supply pin or adjacent pair (5, 15, 24, 29, 41, 50, 59/60, 68/69, 76); pin 64 has C22.
Y1: 12 MHz, e.g. ABM8-272-T3 (CL 10 pF). C35/C36 15 pF, R20 1 k in series with XOUT.
U21 boot flash (XIP CS0), C37 at U21. Holds the firmware and the settings (BASE, SIZE).
J1: USB 2.0. VBUS -> power sheet. SBU unconnected.
R24/R25 5.1 k Rd. R26/R27 33 R series (JLC basic; 27 R is not).
SW5: write protect. Common to GPIO39 (internal pull-up); one throw to ground = protected, the other open.
TP1-TP3: SWD debug pads.
TP4/TP5: spare GPIO46/47, for bench experiments (a second controller's handshake).
